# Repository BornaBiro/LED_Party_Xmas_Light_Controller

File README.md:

# 🎄LED Party And Xmas Light Controller🎄

ATMGEA328P based project for ccontrolling WS2801 RGB LEDs (addressable LEDs with dedicated IC controller, not the ones with built-in controller). It's primarlly used for controlling LED lights for Xmass, but with some code modification can be used for smart ambient light or even a party light (it already has dedicated mode for that, but it does not work properly, more about that later).

## Features 
- microUSB supply
- DC Jack supply (microUSB and DC Jack **CAN'T** be used at the same time!)
- Terminal block for power supply (connected in parallel with DC Jack)
- Analog audio input for MAX4466 microphone breakout
- microSD card reader
- 16x2 I2C LCD
- 2 (3) x LED Channels
- built-in buck regulator for 5V power supply
- RTC for automatic power on and off
- relay output (**for non-mains use only**)
- rotary encoder wuth pushbutton for navigating menu
- buzzer for playing old school Xmas melodies
- CH340 USB to UART IC for easy programming and debugging
- Reset pushbutton
- Addidional pushbutton
- easyC / STEMMA / Qwiic I2C connector for additional I2C devices

There is very neat little feature with this device: it creates same melodies as these old school incandescent Xmas lights. Check that out [here](https://github.com/BornaBiro/LED_Party_Xmas_Light_Controller/blob/dev/Codes/Melody%20Extract/README.md).

## Getting started 🚀
1. Get the board!
2. Get the parts!
3. Solder everything together (except DC-DC converter, **you must set the output voltage to 5V-5.2V first**)
4. Connect DC-DC converter to the power supply and set the output voltage to the 5V-5.2V
5. Solder it to the PCB using the headers
6. Burn the bootloader to the ATMEGA328P (using the test pads at bottom side of the PCB). You can use Arduino as ISP. If you don't know how to use it, check it out [here](https://docs.arduino.cc/built-in-examples/arduino-isp/ArduinoISP).
7. Copy / install provided WS2801 library to the Arduino
8. Open the sketch
9. Set Board as Arduino Nano (Arduino Nano with ATMEPGA328P, old bootloader).
10. Upload the sketch
11. Have fun!

## Contributions to this project
- [ladyM9](https://github.com/ladyM9) - Little help for the timer code (got few ideas on how to approach the problem). Thank you!
- [keith204](https://www.thingiverse.com/keith204/designs) 3D Printed caps for the LEDs - https://www.thingiverse.com/thing:3331268

## Hadrware issues
⚠️**NOTE**⚠️

Before making the CB you have to know that current version of the PCB has _some_ hardware issues. All issues are listed [here](https://github.com/BornaBiro/LED_Party_Xmas_Light_Controller/tree/dev/PCB#hadrware-issues).

⚠️**NOTE**⚠️

I **did not** fix any of these on PCB design, so like I mentioned, you will either need to do these fixes or you will need to make changes on the PCB before you order it.

## Software issues
Software is still in the progress of make it. Since I do not have much free time, do not have high hopes on fixing these. I'll try my best to fix these before Xmas and New Year.
Whole code is written to be non-blocking.

Known issues:
1. Xmas mode and Party Mode are not seperated. Actually on new and updated version only Xmas mode exists!
2. Only xmas mode is working properly
3. Be careful while setting up current Xmas mode, because you can force it into party mode by incrementing it to the Moon and beyond. Not sure if this is a bug or feature. 😆
4. No day selecton on automatic on or off (no date setting either)
5. 3D printed case is still missing.
6. For longer strands with total number of LEDs > 40 one Step Down is not enough.

## To-Do list
1. Try create two different flash images fir different modes that can be loaded into ATMEGA328P from the microSD card
2. Variable/Selectable length of LEDs per output
3. Enable or disable some effects or put them in the list
4. More effects!
5. More timer intervals
6. UART control support

## How to use it
The device has two/three WS2802 LEDs outputs. Number of LEDs per output can be configured in the [code](Codes/Arduino%20Code/led_party_xmas_light_controller/defines.h), STRAND1, STRAND2 and STRAND3. Third channel can be used for relay output (selected by default) or for one more channel for LEDs. On first start up it will set all setting to default ones. Every settting is stored in ATMEGA328P EEPROM. To enter menu, press Rotary Enc. To go thorugh menu, rotate rotary encoder. To enter settings, press the encoder again. Rotate it to set parameters. To go on the next parameter press the encoder. To exit setting, wait or simply keep pressing until `>` is not visable anymore. `>` shows what parametes is currently being set. To exit menu, wait or go to `Exit`. The menu will timeout as well as the backlight.

### Menu
  - Current mode: Shows current mode - Only Xmas for now
  - Current setting: Shows what light mode is currently active (same on the main menu along with the clock)
  - Frame speed: To slow or speed up the current animation (in percent)
  - Animation dur.: How long to keep current light effect (in seconds)
  - Auto Change: If enabled it will go though all light modes automatically.
  - Melody: If enabled it will play the melody if light mode has melody.
  - Auto Start: If set on `Auto`, light will power up automaticaly accordingly on `Activation Time` intervals. Relay and LEDs are seperated. `On` will keeps LEDs or relay on all the time overriding timer intervals.
  - Set Time: Set the time on RTC.
  - Activation Time: Set the times when the device will be powered on. First time is when device will be enabled, second is when the deivce disable LEDs/Relay. Y/N is if this timeslot it even enabled or not.
  - Exit: Exit menu.

## Few more images

## Licence
This project uses MIT licence. It is provided as is - no warranty is given. In other words - use it at your own risk.
You can use this project, change it, modify it, but source must be listed (this github repo) as well as the author name.

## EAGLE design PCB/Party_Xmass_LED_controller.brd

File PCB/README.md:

PCB CAD files are made with EAGLE. I will add gerbers files later (if needed).

### Hadrware issues
Yeah, this things happen, it doesn't work from the first try, so there are some fixes you need to make in order to your PCB work properly.

1. microUSB connector does not fit. I use wrong footprint. Used microUSB connector is [920-E52A2021S10100](https://www.lcsc.com/product-detail/USB-Connectors_Jing-Extension-of-the-Electronic-Co-920-E52A2021S10100_C10418.html)
2. Missing SMD 10uF MLCC at DC input

3. Missing debounce capacitor on rotary enncoder pushbutton from pin to GND (100nF)

4. Analog audio part... Ohh boy... AVCC and AREF sholud be seperated (AVCC should be on 5V but AREF should be on 3V3), bias curcuit is missing filtering, MIC and bias must be supplied from 3V3.

5. No GND at 3V3 VREG... This one hurts the most...

6. Swapped CLK_OUT and CLK_OE... and this one...

7. In order to make MIC breakout to work properly (so it does not capture noise from the power supply), cut the MIC supply trace and add 10uF 1206 MLCC.

8. Added two 1206 10uF MLCC at the output of the DC-DC converter to reduce high frequency noise.

9. Some of these DC-DC converters are noisy. If needed, add 470uF at the output of the DC-DC converter.

**NOTE** I did not fix any of these on PCB design, so like I mentioned, you will either need to do these fixes or you will need to make changes on the PCB before you order it.

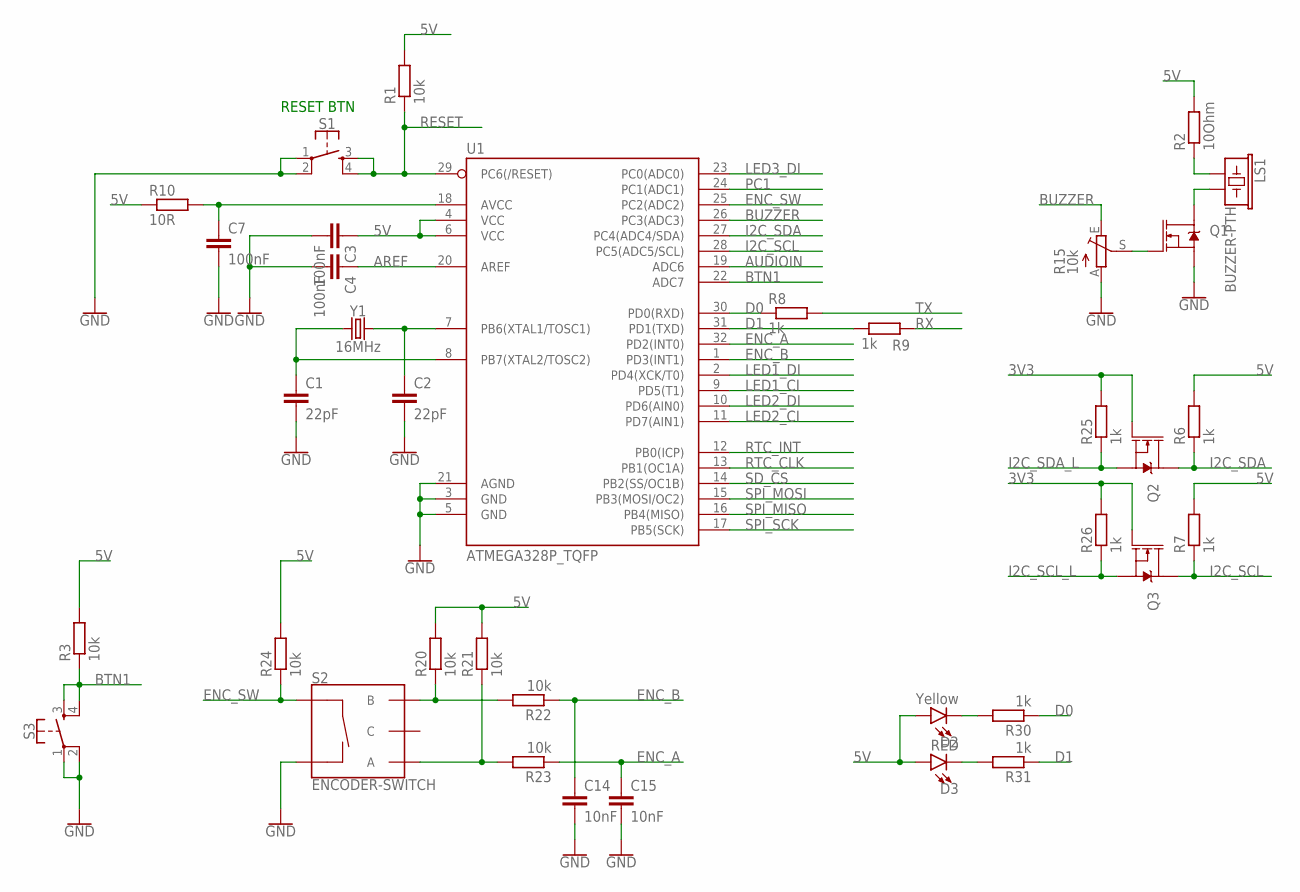
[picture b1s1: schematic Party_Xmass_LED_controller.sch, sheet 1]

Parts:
C1, C2: 22pF; C0603
C3, C4, C7: 100nF; C0603
C14, C15: 10nF; C0603
D2: Yellow; LED-0603
D3: RED; LED-0603
LS1: BUZZER-PTH; BUZZER-12MM
Q1, Q2, Q3: MOSFET-NCH-BSS138; SOT23-3
R1, R3, R20, R21, R22, R23, R24: 10k; R0603
R2: 10Ohm; R0603
R6, R7, R8, R9, R25, R26, R30, R31: 1k; R0603
R10: 10R; R0603
R15: 10k; CA6V
S1, S3: MOMENTARY-SWITCH-SPST-2-SMD-5.2MM; TACTILE_SWITCH_SMD_5.2MM
S2: ENCODER-SWITCH; ROTARY_ENC_PLAIN
U1: ATMEGA328P_TQFP; TQFP32-08
Y1: 16MHz; CRYSTAL-SMD-5X3.2-4PAD

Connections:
3V3: Q2.1 (G), Q3.1 (G), R25.2, R26.2; also elsewhere on the board
5V: C3.1, D2.A, D3.A, R1.2, R2.2, R3.2, R6.2, R7.2, R10.1, R20.2, R21.2, R24.2, U1.4 (VCC), U1.6 (VCC); also elsewhere on the board
AREF: C4.1, U1.20 (AREF); also elsewhere on the board
AUDIOIN: U1.19 (ADC6); also elsewhere on the board
BTN1: R3.1, S3.3, S3.4, U1.22 (ADC7)
BUZZER: R15.E, U1.26 (PC3(ADC3))
D0: R8.1, R30.1, U1.30 (PD0(RXD))
D1: R9.1, R31.1, U1.31 (PD1(TXD))
ENC_A: C15.1, R23.1, U1.32 (PD2(INT0))
ENC_B: C14.1, R22.1, U1.1 (PD3(INT1))
ENC_SW: R24.1, S2.SW+, U1.25 (PC2(ADC2))
GND: C1.2, C2.2, C3.2, C4.2, C7.2, C14.2, C15.2, Q1.2 (S), R15.A, S1.1, S1.2, S2.SW-, S3.1, S3.2, U1.3 (GND), U1.5 (GND), U1.21 (AGND); also elsewhere on the board
I2C_SCL: Q3.3 (D), R7.1, U1.28 (PC5(ADC5/SCL)); also elsewhere on the board
I2C_SCL_L: Q3.2 (S), R26.1; also elsewhere on the board
I2C_SDA: Q2.3 (D), R6.1, U1.27 (PC4(ADC4/SDA)); also elsewhere on the board
I2C_SDA_L: Q2.2 (S), R25.1; also elsewhere on the board
LED1_CI: U1.9 (PD5(T1)); also elsewhere on the board
LED1_DI: U1.2 (PD4(XCK/T0)); also elsewhere on the board
LED2_CI: U1.11 (PD7(AIN1)); also elsewhere on the board
LED2_DI: U1.10 (PD6(AIN0)); also elsewhere on the board
LED3_DI: U1.23 (PC0(ADC0)); also elsewhere on the board
unnamed: R20.1, R22.2, S2.B
unnamed: LS1.- (2), Q1.3 (D)
unnamed: LS1.+ (1), R2.1
unnamed: C2.1, U1.7 (PB6(XTAL1/TOSC1)), Y1.3 (2)
unnamed: C1.1, U1.8 (PB7(XTAL2/TOSC2)), Y1.1
unnamed: C7.1, R10.2, U1.18 (AVCC)
unnamed: R21.1, R23.2, S2.A
unnamed: Q1.1 (G), R15.S
unnamed: D2.C, R30.2
unnamed: D3.C, R31.2
PC1: U1.24 (PC1(ADC1)); also elsewhere on the board
RESET: R1.1, S1.3, S1.4, U1.29 (PC6(/RESET)); also elsewhere on the board
RTC_CLK: U1.13 (PB1(OC1A)); also elsewhere on the board
RTC_INT: U1.12 (PB0(ICP)); also elsewhere on the board
RX: R9.2; also elsewhere on the board
SD_CS: U1.14 (PB2(SS/OC1B)); also elsewhere on the board
SPI_MISO: U1.16 (PB4(MISO)); also elsewhere on the board
SPI_MOSI: U1.15 (PB3(MOSI/OC2)); also elsewhere on the board
SPI_SCK: U1.17 (PB5(SCK)); also elsewhere on the board
TX: R8.2; also elsewhere on the board

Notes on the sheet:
RESET BTN

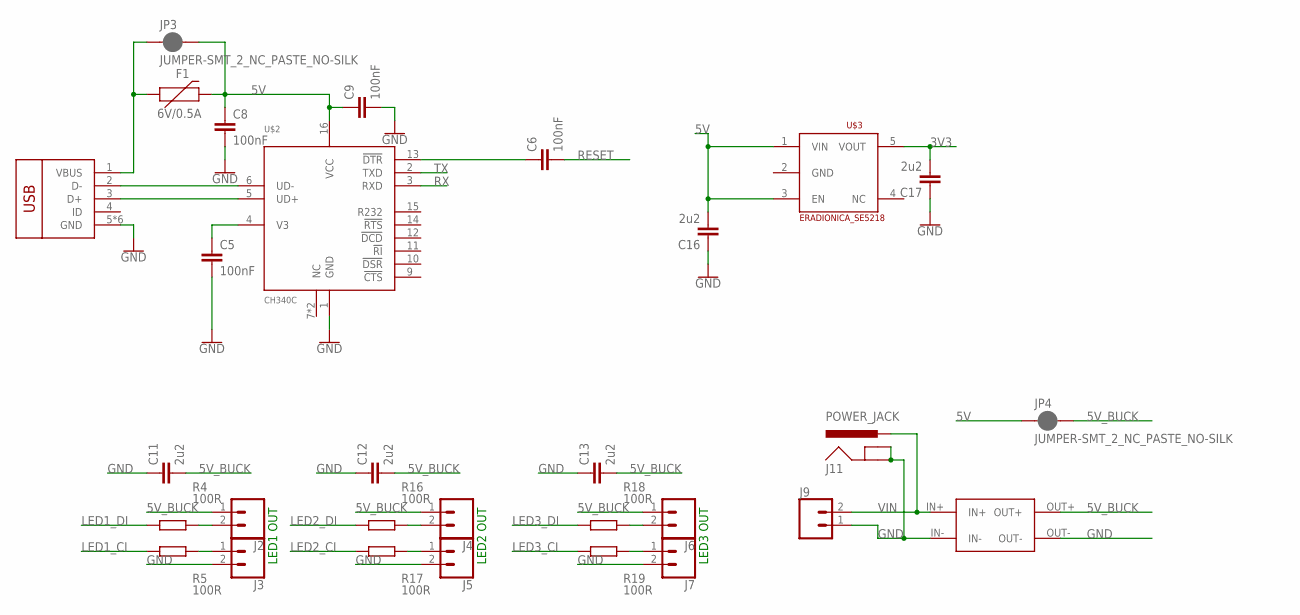
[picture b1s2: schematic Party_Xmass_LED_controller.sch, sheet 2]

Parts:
C5, C6, C8, C9: 100nF; C0603
C11, C12, C13, C16, C17: 2u2; C0603
F1: 6V/0.5A; 1206
J2, J3, J4, J5, J6, J7: CONN_023.5MM; SCREWTERMINAL-3.5MM-2
J9: CONN_025MM; SCREWTERMINAL-5MM-2
J11: POWER_JACK; POWER_JACK_PTH
JP3, JP4: JUMPER-SMT_2_NC_PASTE_NO-SILK; SMT-JUMPER_2_NC_PASTE_NO-SILK
R4, R5, R16, R17, R18, R19: 100R; R0603
U$1: ERADIONICA_USB-MICRO; ERADIONICA_U-F-M5DD-Y-L
U$2: CH340C; SOP-16
U$3: ERADIONICA_SE5218; ERADIONICA_SOT23-5
U$4: STEPDOWN_MODULE_LM2596

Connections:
3V3: C17.2, U$3.5 (VOUT); also elsewhere on the board
5V: C8.1, C9.1, C16.2, F1.2, JP3.2, JP4.1, U$2.16 (VCC), U$3.1 (VIN), U$3.3 (EN); also elsewhere on the board
5V_BUCK: C11.2, C12.2, C13.2, J2.1, J4.1, J6.1, JP4.2, U$4.OUT+; also elsewhere on the board
GND: C5.2, C8.2, C9.2, C11.1, C12.1, C13.1, C16.1, C17.1, J3.2, J5.2, J7.2, J9.1, J11.GND, J11.GNDBREAK, U$1.5 (GND), U$1.PAD (GND), U$1.SHIELD1 (GND), U$1.SHIELD2 (GND), U$1.SHIELD3 (GND), U$1.SHIELD4 (GND), U$2.1 (GND), U$4.IN-, U$4.OUT-; also elsewhere on the board
LED1_CI: R5.1; also elsewhere on the board
LED1_DI: R4.1; also elsewhere on the board
LED2_CI: R17.1; also elsewhere on the board
LED2_DI: R16.1; also elsewhere on the board
LED3_CI: R19.1; also elsewhere on the board
LED3_DI: R18.1; also elsewhere on the board
unnamed: C5.1, U$2.4 (V3)
unnamed: C6.1, U$2.13 (!DTR)
unnamed: U$1.2 (D-), U$2.6 (UD-)
unnamed: U$1.3 (D+), U$2.5 (UD+)
unnamed: F1.1, JP3.1, U$1.1 (VBUS)
unnamed: J2.2, R4.2
unnamed: J3.1, R5.2
unnamed: J4.2, R16.2
unnamed: J5.1, R17.2
unnamed: J6.2, R18.2
unnamed: J7.1, R19.2
RESET: C6.2; also elsewhere on the board
RX: U$2.3 (RXD); also elsewhere on the board
TX: U$2.2 (TXD); also elsewhere on the board
VIN: J9.2, J11.PWR, U$4.IN+

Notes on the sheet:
LED1 OUT
LED2 OUT
LED3 OUT

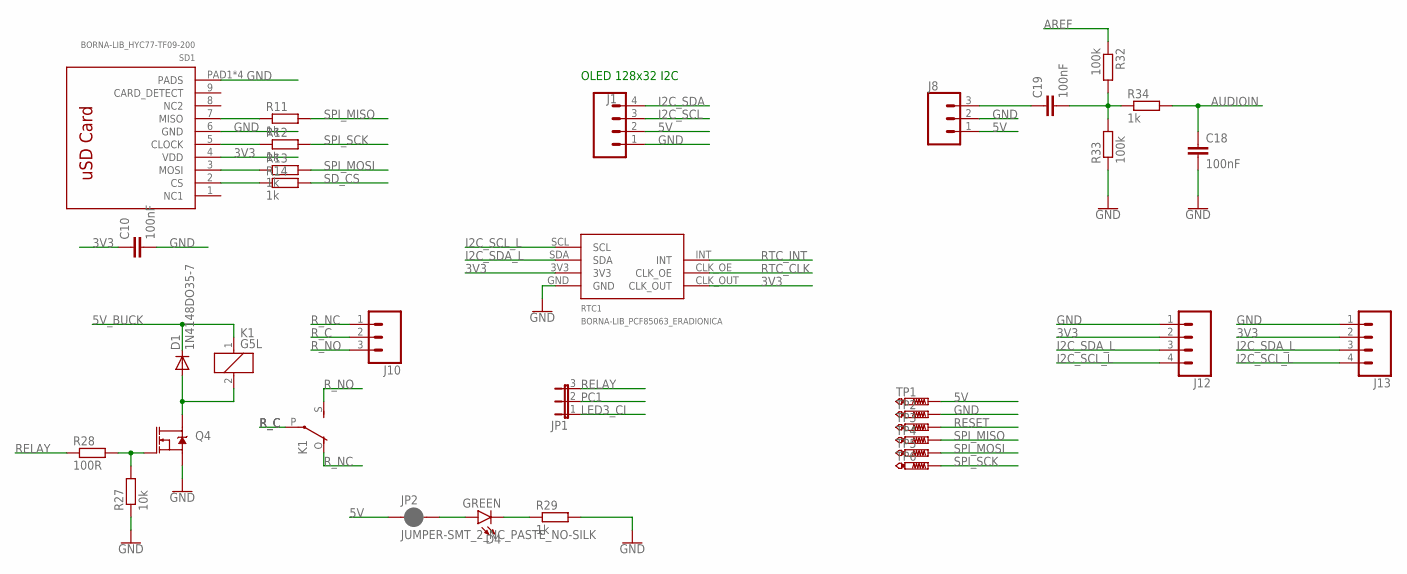
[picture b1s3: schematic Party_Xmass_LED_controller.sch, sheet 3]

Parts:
C10, C18, C19: 100nF; C0603
D1: 1N4148DO35-7; DO35-7
D4: GREEN; LED-0603
J1: CONN_04; 1X04
J8: CONN_03; 1X03
J10: CONN_03SCREW; SCREWTERMINAL-3.5MM-3
J12, J13: CONN_04SMD2; 1X04_1MM_RA
JP1: JP2E; JP2
JP2: JUMPER-SMT_2_NC_PASTE_NO-SILK; SMT-JUMPER_2_NC_PASTE_NO-SILK
K1: G5L; G5LE
Q4: MOSFET-NCH-BSS138; SOT23-3
R11, R12, R13, R14, R29, R34: 1k; R0603
R27: 10k; R0603
R28: 100R; R0603
R32, R33: 100k; R0603
RTC1: BORNA-LIB_PCF85063_ERADIONICA
SD1: BORNA-LIB_HYC77-TF09-200; BORNA-LIB_MICROSD_HOLDER
TP1, TP2, TP3, TP4, TP5, TP6: PTR1B1,27; B1,27

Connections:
3V3: C10.1, J12.2, J13.2, RTC1.3V3, RTC1.CLK_OUT, SD1.4 (VDD); also elsewhere on the board
5V: J1.2, J8.1, JP2.1, TP1.TP; also elsewhere on the board
5V_BUCK: D1.C, K1.1; also elsewhere on the board
AREF: R32.1; also elsewhere on the board
AUDIOIN: C18.1, R34.2; also elsewhere on the board
GND: C10.2, C18.2, J1.1, J8.2, J12.1, J13.1, Q4.2 (S), R27.1, R29.2, R33.1, RTC1.GND, SD1.6 (GND), SD1.PAD1 (PADS), SD1.PAD2 (PADS), SD1.PAD3 (PADS), SD1.PAD4 (PADS), TP2.TP; also elsewhere on the board
I2C_SCL: J1.3; also elsewhere on the board
I2C_SCL_L: J12.4, J13.4, RTC1.SCL; also elsewhere on the board
I2C_SDA: J1.4; also elsewhere on the board
I2C_SDA_L: J12.3, J13.3, RTC1.SDA; also elsewhere on the board
LED3_CI: JP1.1; also elsewhere on the board
MICIN: C19.2, R32.2, R33.2, R34.1
unnamed: C19.1, J8.3
unnamed: R11.1, SD1.7 (MISO)
unnamed: R12.1, SD1.5 (CLOCK)
unnamed: R13.1, SD1.3 (MOSI)
unnamed: R14.1, SD1.2 (CS)
unnamed: Q4.1 (G), R27.2, R28.2
unnamed: D1.A, K1.2, Q4.3 (D)
unnamed: D4.A, JP2.2
unnamed: D4.C, R29.1
PC1: JP1.2; also elsewhere on the board
RELAY: JP1.3, R28.1
RESET: TP3.TP; also elsewhere on the board
RTC_CLK: RTC1.CLK_OE; also elsewhere on the board
RTC_INT: RTC1.INT; also elsewhere on the board
R_C: J10.2, K1.P
R_NC: J10.1, K1.O
R_NO: J10.3, K1.S
SD_CS: R14.2; also elsewhere on the board
SPI_MISO: R11.2, TP4.TP; also elsewhere on the board
SPI_MOSI: R13.2, TP5.TP; also elsewhere on the board
SPI_SCK: R12.2, TP6.TP; also elsewhere on the board

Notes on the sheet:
OLED 128x32 I2C

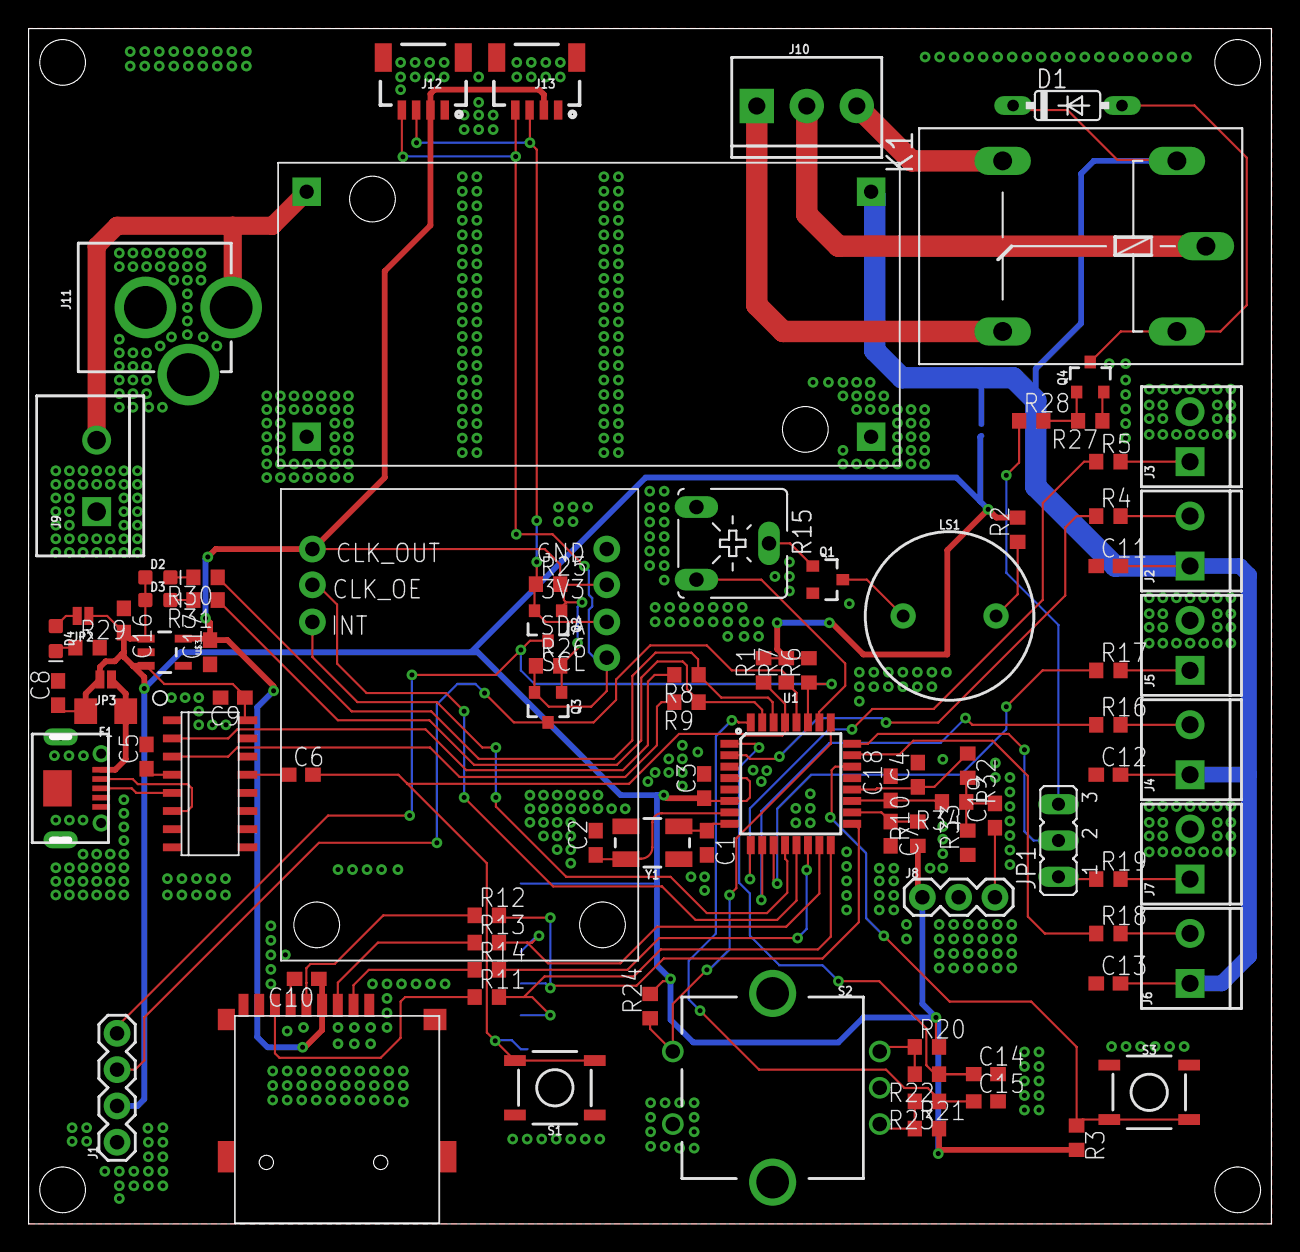
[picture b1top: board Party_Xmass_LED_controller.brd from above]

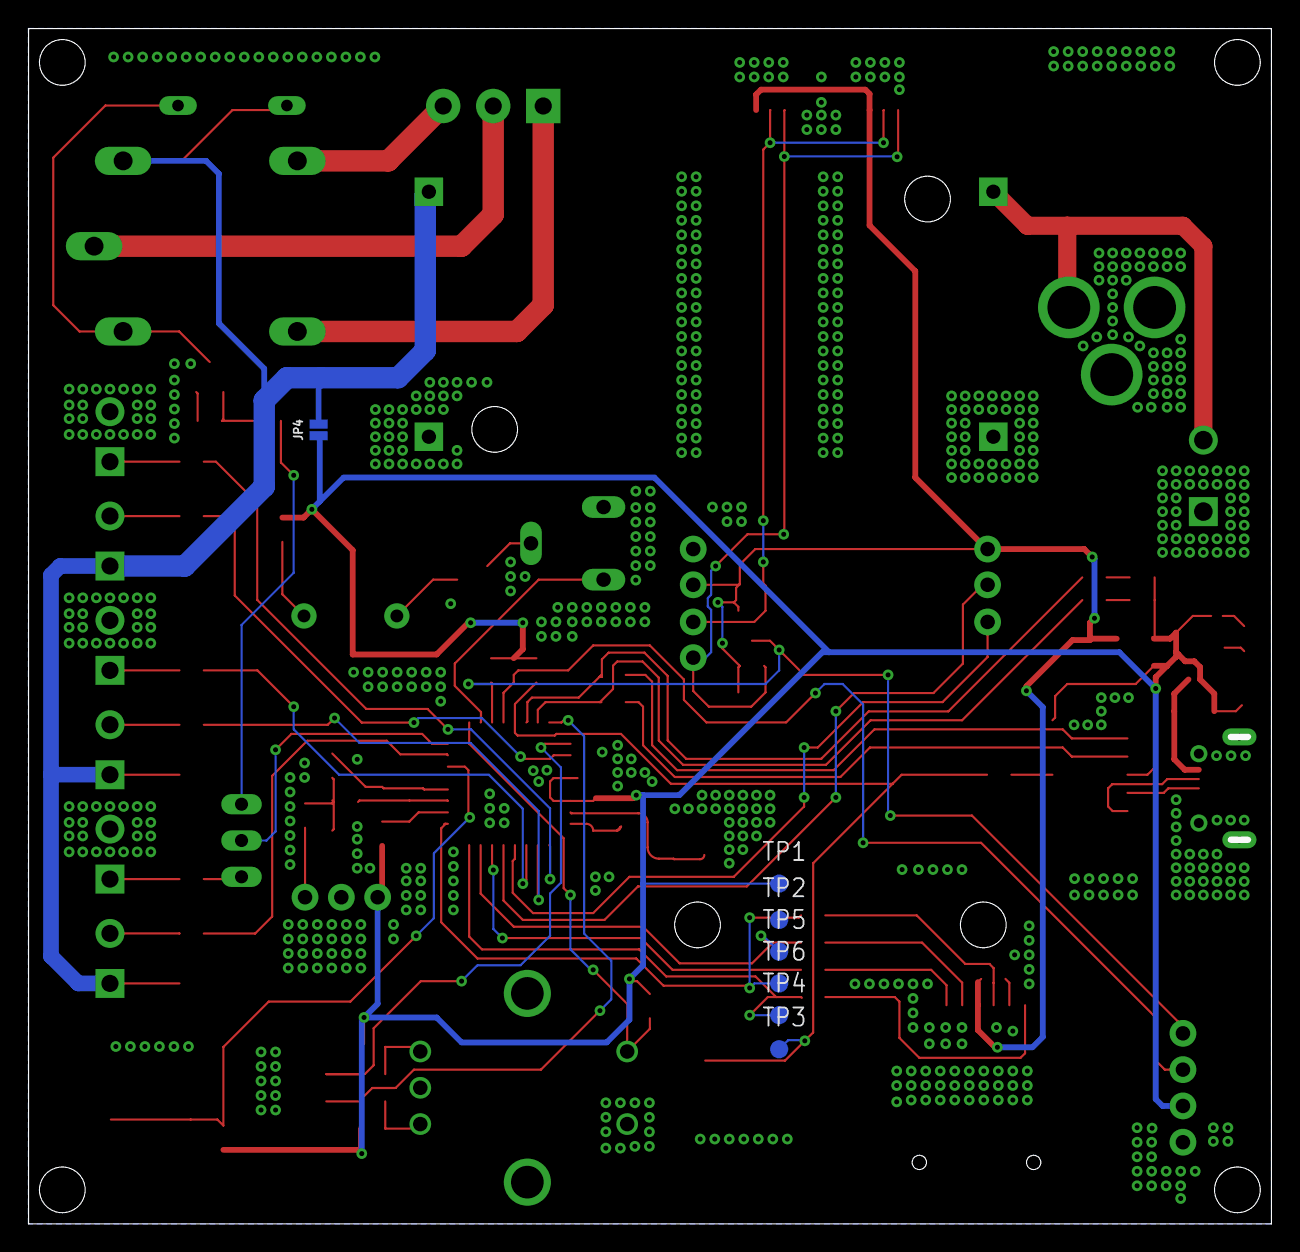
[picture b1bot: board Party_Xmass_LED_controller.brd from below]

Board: 2 copper layers, 86.5 x 83.2 mm, 98 parts (7 on the bottom side), 69 nets.

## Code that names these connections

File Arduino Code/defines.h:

// Select only one of these two
#define USE_RELAY_OUTPUT
//#define USE_WS3_OUTPUT

#if defined(USE_RELAY_OUTPUT) && defined(USE_WS3_OUTPUT)
#error "Both relay output and WS3_CLK are selected! Pick only one!"
#endif

// Sound
#define BUZZER   A3
#define AUDIO_IN A6

// Lights
#define WS1_DAT 4
#define WS1_CLK 5
#define WS2_DAT 6
#define WS2_CLK 7
#define WS3_DAT A0
#define WS3_CLK A1 // If it's used

// Number of addressable LEDs on each WS output
#define STRAND1     20
#define STRAND2     20
#define SRRAND3     20

// Inputs/Outputs
#define ENC_A      2  // It's also INT0
#define ENC_B      3  // It's also INT1
#define ENC_SW     A2 // It's also PCINT10
#define RELAY      A1 // If it's used
#define BTN_1      A7 // NOTE: It's on analog in only!
#define SD_CS      10
#define RTC_INT    8  // It's also PCINT0
#define RTC_CLKOUT 9  // It's also PCINT1

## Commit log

2021-12-11 Folder structure, added LEDs reacting to audio, added library for LEDs
2021-12-11 Added Sch PDF
2021-12-11 Code for reacting LEDs to music is divided into multiple files. Added controller.h and audio.h.
2021-12-11 Do not turn on relay (for debug purpose only).
2021-12-20 Fixed audio, added multiple LED modes, added simple GUI, added LED colors
2021-12-21 More LED modes, added OLED screen saver, added HSV to RGB conversion, new GUI system.
2022-12-04 Many changes, creating almost new code.
    - Changed display. From 128x32 OELD to 16x2 LCD to save the memory
    - Added men: Added whole new menu code and structure
    - Fixed audio processing: Now reaction to the audio works perfectly fine.
    - Fixed RTC bug
    - Added code for the buzzer
    -
2022-12-04 More optimizations
    TODO
    - All stings needs to be stored in FLASH
    - Create function that checks _currentItem
2022-12-19 EEPRM added, xmas songs added, fixed automatic power on/off.
2022-12-23 Almost finished (missing music and full party mode)
2022-12-23 Added melody mode (XMAS MODE 5)
2022-12-23 Added pause between songs.
2022-12-23 Fixed overflow (that caused modes not to change).
2022-12-26 Added code contributions
2023-01-04 Added party mode (that broke everything)
2023-10-15 Switched to the external analog reference.
2023-10-28 Added images, folder structure change.
2023-10-28 Added script for melody extraction.
2023-10-29 Added images, added extracted data.
2023-12-18 Added test codes.
2023-12-19 Added more modes, added automatic mode change select, added one more led channel.
2023-12-21 One more mode.
2023-12-21 Xmas controller finally done!
2023-12-21 Fixed bug in the mode settings.
2023-12-22 LED controller is off by default, RTC Alarm code is removed, check for the mode change.
2024-12-05 Added new effect (candles), added LCD I2C library.
2024-12-29 Updated readme.
2024-12-30 Added 3D file.

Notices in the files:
parts and their libraries:
SparkFun-Connectors: Licensing: Creative Commons ShareAlike 4.0 International - https://creativecommons.org/licenses/by-sa/4.0
